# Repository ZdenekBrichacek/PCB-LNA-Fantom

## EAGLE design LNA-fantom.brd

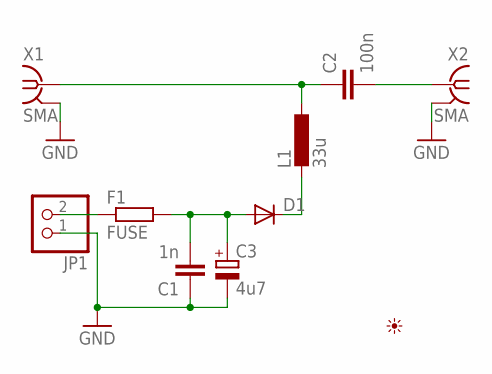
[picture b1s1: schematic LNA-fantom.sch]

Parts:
C1: 1n; C0805
C2: 100n; C0805
C3: 4u7; SMC_A
D1: DIODE-MINIMELF; MINIMELF
F1: FUSE; R1210
JP1: PINHD-1X2; 1X02
L1: 33u; POWER-CHOKE_WE-TPC
U$1: PICTO_1
X1, X2: SMA; J502-ND-142-0701-801/806

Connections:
GND: C1.1, C3.-, JP1.1, X1.G@1 (2), X1.G@2 (2), X1.G@3 (2), X1.G@4 (2), X2.G@1 (2), X2.G@2 (2), X2.G@3 (2), X2.G@4 (2)
unnamed: F1.1, JP1.2
unnamed: C1.2, C3.+, D1.A, F1.2
unnamed: C2.1, L1.1, X1.1
unnamed: C2.2, X2.1
unnamed: D1.C, L1.2

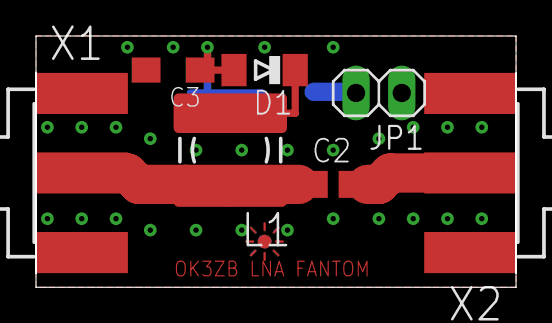
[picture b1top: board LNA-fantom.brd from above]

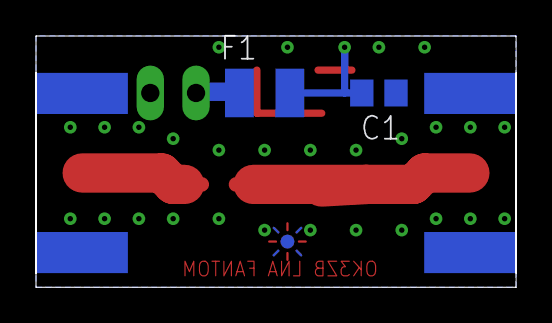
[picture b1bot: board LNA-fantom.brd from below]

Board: 2 copper layers, 26.7 x 14.0 mm, 10 parts (2 on the bottom side), 6 nets.

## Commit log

2017-10-10 :neckbeard: Added .gitattributes & .gitignore files
2017-10-10 Initial version
